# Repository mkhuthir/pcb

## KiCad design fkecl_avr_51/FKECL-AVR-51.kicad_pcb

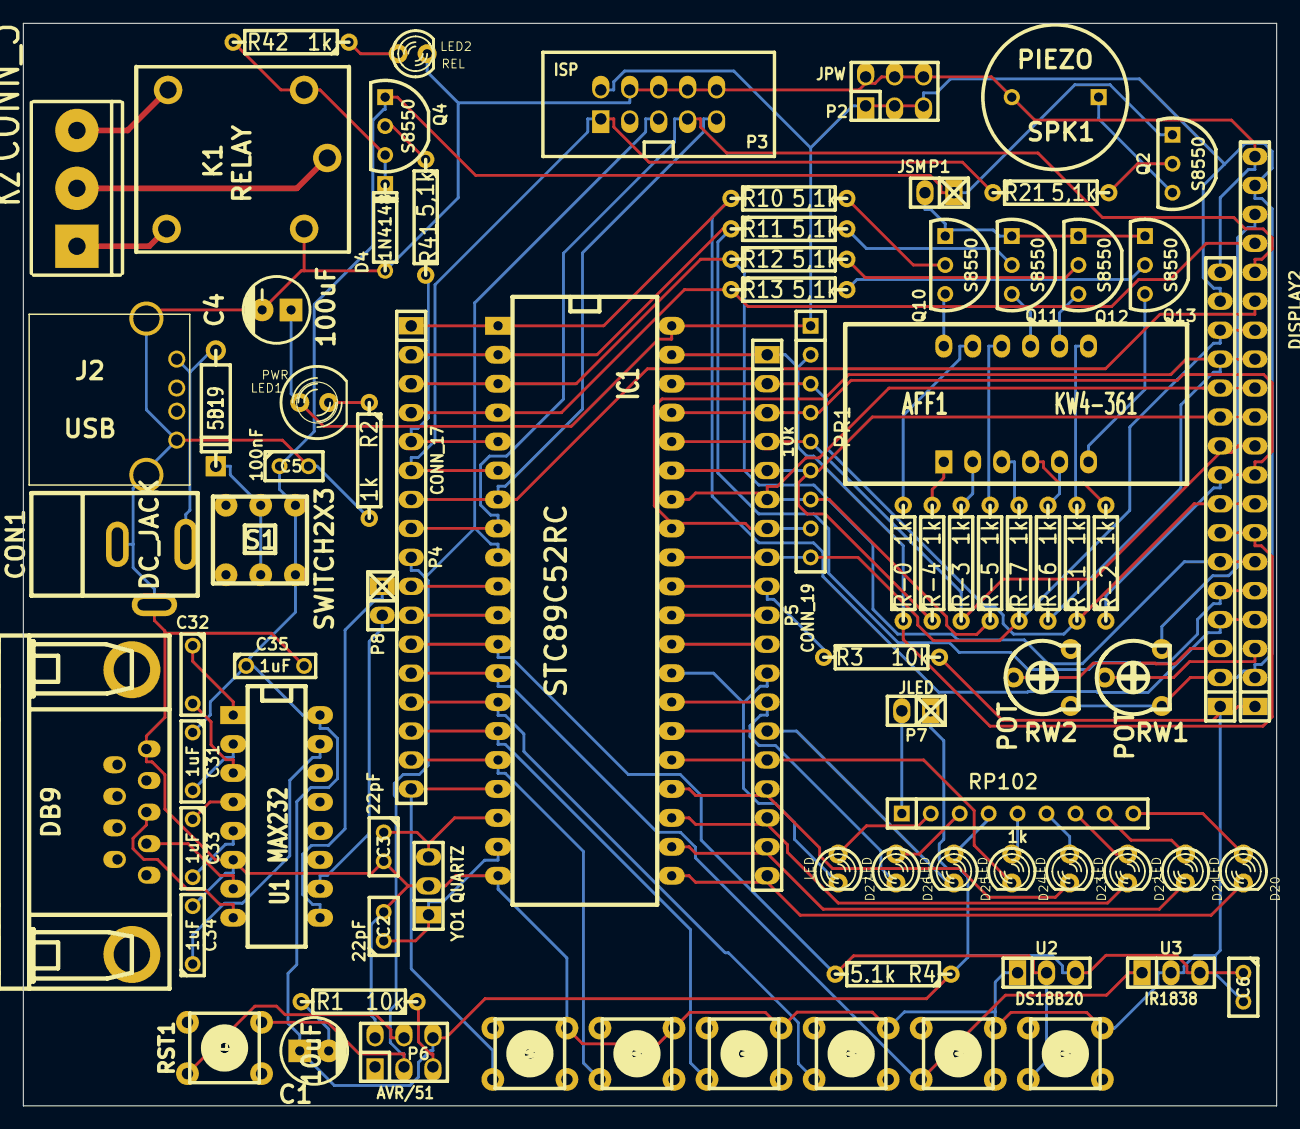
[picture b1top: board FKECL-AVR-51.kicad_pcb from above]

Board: 2 copper layers, 110.0 x 95.0 mm, 82 parts (0 on the bottom side), 94 nets.

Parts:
AFF1: KW4-361
C1: 10uF; CP_SMALL
C2, C3: 22pF; C1
C4: 100uF; CP_SMALL
C5, C6: 100nF; C1
C31, C32, C33, C34, C35: 1uF; C2
CON1: DC_JACK; dc_socket
D1: 5819; D4
D4: 1N4148; D3
D20, D21, D22, D23, D24, D25, D26, D27: LED; LED-3MM
DISPLAY1: LCD16X2; pin_socket_16
DISPLAY2: LCD12864/240128; pin_socket_20
IC1: STC89C52RC; DIP-40__600_ELL
J1: DB9; DB_9F
J2: USB; USB_A
K1: RELAY; RELAY-1RG
K2: CONN_3; BORN3
LED1: PWR; LED-5MM
LED2: REL; LED-3MM
P1: JSM; pin_strip_2
P2: JPW; pin_strip_3x2
P3: ISP; conn_strip_5x2
P4: CONN_17; pin_strip_17
P5: CONN_19; PIN_STRIP_19
P6: AVR/51; pin_strip_3x2
P7: JLED; pin_strip_2
P8: CONN_2; pin_strip_2
PR1: 10k; r_pack8
Q2, Q4, Q10, Q11, Q12, Q13: S8550; TO92_LINE
R1, R3: 10k; R4
R2, R42: 1k; R4
R4: 5.1k; R4
R10, R11, R12, R13, R21, R41: 5,1k; R4
R-0, R-1, R-2, R-3, R-4, R-5, R-6, R-7: 1k; R4
RP102: 1k; r_pack8
RST1: RET; PUSH_SW_TH
RW1, RW2: POT; rv_hor
S1: SWITCH2X3; Switch2x3
SPK1: PIEZO; BUZZER
SW1, SW2, SW3, SW4, SW5, SW6: PUSH_SW_TH
U1: MAX232; DIP-16__300_ELL
U2: DS18B20; pin_socket_3
U3: IR1838; pin_socket_3
YO1: QUARTZ; pin_socket_3

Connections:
/ALE: IC1.30, P5.10
/Dig1: AFF1.12, Q10.3
/Dig2: AFF1.9, Q11.3
/Dig3: AFF1.8, Q12.3
/Dig4: AFF1.6, Q13.3
/EA: IC1.31, P5.9, R3.1
/P0.0: DISPLAY1.7, DISPLAY2.7, IC1.39, P5.1, PR1.2, R-0.1
/P0.1: DISPLAY1.8, DISPLAY2.8, IC1.38, P5.2, PR1.3, R-1.1
/P0.2: DISPLAY1.9, DISPLAY2.9, IC1.37, P5.3, PR1.4, R-2.1
/P0.3: DISPLAY1.10, DISPLAY2.10, IC1.36, P5.4, PR1.5, R-3.1
/P0.4: DISPLAY1.11, DISPLAY2.11, IC1.35, P5.5, PR1.6, R-4.1
/P0.5: DISPLAY1.12, DISPLAY2.12, IC1.34, P5.6, PR1.7, R-5.1
/P0.6: DISPLAY1.13, DISPLAY2.13, IC1.33, P5.7, PR1.8, R-6.1
/P0.7: DISPLAY1.14, DISPLAY2.14, IC1.32, P5.8, PR1.9, R-7.1
/P1.0: DISPLAY1.4, DISPLAY2.4, IC1.1, P4.1, R10.1
/P1.1: DISPLAY1.5, DISPLAY2.5, IC1.2, P4.2, R11.1
/P1.2: DISPLAY1.6, DISPLAY2.6, IC1.3, P4.3, R12.1
/P1.3: DISPLAY2.17, IC1.4, P4.4, R13.1
/P1.4: IC1.5, P4.5, R41.2
/P1.5: IC1.6, P3.1, P4.6, R21.1
/P1.6: DISPLAY2.15, IC1.7, P3.9, P4.7
/P1.7: DISPLAY2.16, IC1.8, P3.7, P4.8
/P2.0: D20.2, IC1.21, P5.19
/P2.1: D21.2, IC1.22, P5.18
/P2.2: D22.2, IC1.23, P5.17
/P2.3: D23.2, IC1.24, P5.16
/P2.4: D24.2, IC1.25, P5.15
/P2.5: D25.2, IC1.26, P5.14
/P2.6: D26.2, IC1.27, P5.13
/P2.7: D27.2, IC1.28, P5.12
/P3.0: IC1.10, P4.10
/P3.1: IC1.11, P4.11
/P3.2: IC1.12, P4.12, R4.2, SW6.1, U2.2
/P3.3: IC1.13, P4.13, SW5.1, U3.1
/P3.4: IC1.14, P4.14, SW4.1
/P3.5: IC1.15, P4.15, SW3.1
/P3.6: IC1.16, P4.16, SW2.1
/P3.7: IC1.17, P4.17, SW1.1
/PSEN: IC1.29, P5.11
/RST: IC1.9, P3.5, P4.9, P6.3, RST1.2
/a: AFF1.11, R-0.2
/b: AFF1.7, R-1.2
/c: AFF1.4, R-2.2
/d: AFF1.2, R-3.2
/dp: AFF1.3, R-7.2
/e: AFF1.1, R-4.2
/f: AFF1.10, R-5.2
/g: AFF1.5, R-6.2
GND: C2.2, C3.2, C4.2, C5.2, C6.2, C34.2, C35.2, CON1.1, CON1.2, D4.1, DISPLAY1.1, DISPLAY1.16, DISPLAY2.1, DISPLAY2.20, IC1.20, J1.5, J2.4, J2.5, J2.6, K1.B1, LED2.2, P2.2, P2.4, P2.6, P3.4, P3.6, P3.8, P3.10, P6.2, R2.2, R3.2, SPK1.2, SW1.2, SW2.2, SW3.2, SW4.2, SW5.2, SW6.2, U1.6, U2.1, U3.2, YO1.2
unnamed: D1.2, S1.B, S1.Y
unnamed: DISPLAY1.3, RW2.2
unnamed: C2.1, IC1.19, YO1.1
unnamed: C3.1, IC1.18, YO1.3
unnamed: P6.4, RST1.1
unnamed: P6.5, R1.1
unnamed: CON1.3, D1.1, J2.1
unnamed: Q2.3, SPK1.1
unnamed: DISPLAY2.18, RW1.3
unnamed: DISPLAY2.3, RW1.2
unnamed: Q2.2, R21.2
unnamed: C1.2, R1.2
unnamed: P8.2, U1.10
unnamed: P8.1, U1.9
unnamed: J1.2, U1.7
unnamed: J1.3, U1.8
unnamed: LED1.2, R2.1
unnamed: P1.2, Q10.1, Q11.1, Q12.1, Q13.1
unnamed: Q13.2, R13.2
unnamed: Q12.2, R12.2
unnamed: Q11.2, R11.2
unnamed: Q10.2, R10.2
unnamed: C34.1, U1.15
unnamed: D20.1, RP102.9
unnamed: D21.1, RP102.8
unnamed: D22.1, RP102.7
unnamed: D23.1, RP102.6
unnamed: D24.1, RP102.5
unnamed: D25.1, RP102.4
unnamed: D26.1, RP102.3
unnamed: D27.1, RP102.2
unnamed: P7.2, RP102.1
unnamed: K1.NF, K2.1
unnamed: K1.NA, K2.3
unnamed: K1.C, K2.2
unnamed: LED2.1, R42.1
unnamed: Q4.2, R41.1
unnamed: D4.2, K1.B2, Q4.3, R42.2
unnamed: C32.1, U1.1
unnamed: C32.2, U1.3
unnamed: C33.1, U1.4
unnamed: C33.2, U1.5
unnamed: C31.2, U1.2
VCC: C4.1, DISPLAY1.2, DISPLAY1.15, DISPLAY2.2, DISPLAY2.19, IC1.40, LED1.1, P2.1, P2.3, P2.5, P3.2, PR1.1, RW1.1, RW2.1
VDD: C1.1, C5.1, C6.1, C31.1, C35.1, P1.1, P6.6, P7.1, Q2.1, Q4.1, R4.1, S1.A1, S1.X1, U1.16, U2.3, U3.3

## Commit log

2023-10-14 STC89C52RC Dev Board
2023-10-16 test
